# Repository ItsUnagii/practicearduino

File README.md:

# practicearduino

A custom Arduino PCB using a ATmega328P-A microcontroller made for personal practice.

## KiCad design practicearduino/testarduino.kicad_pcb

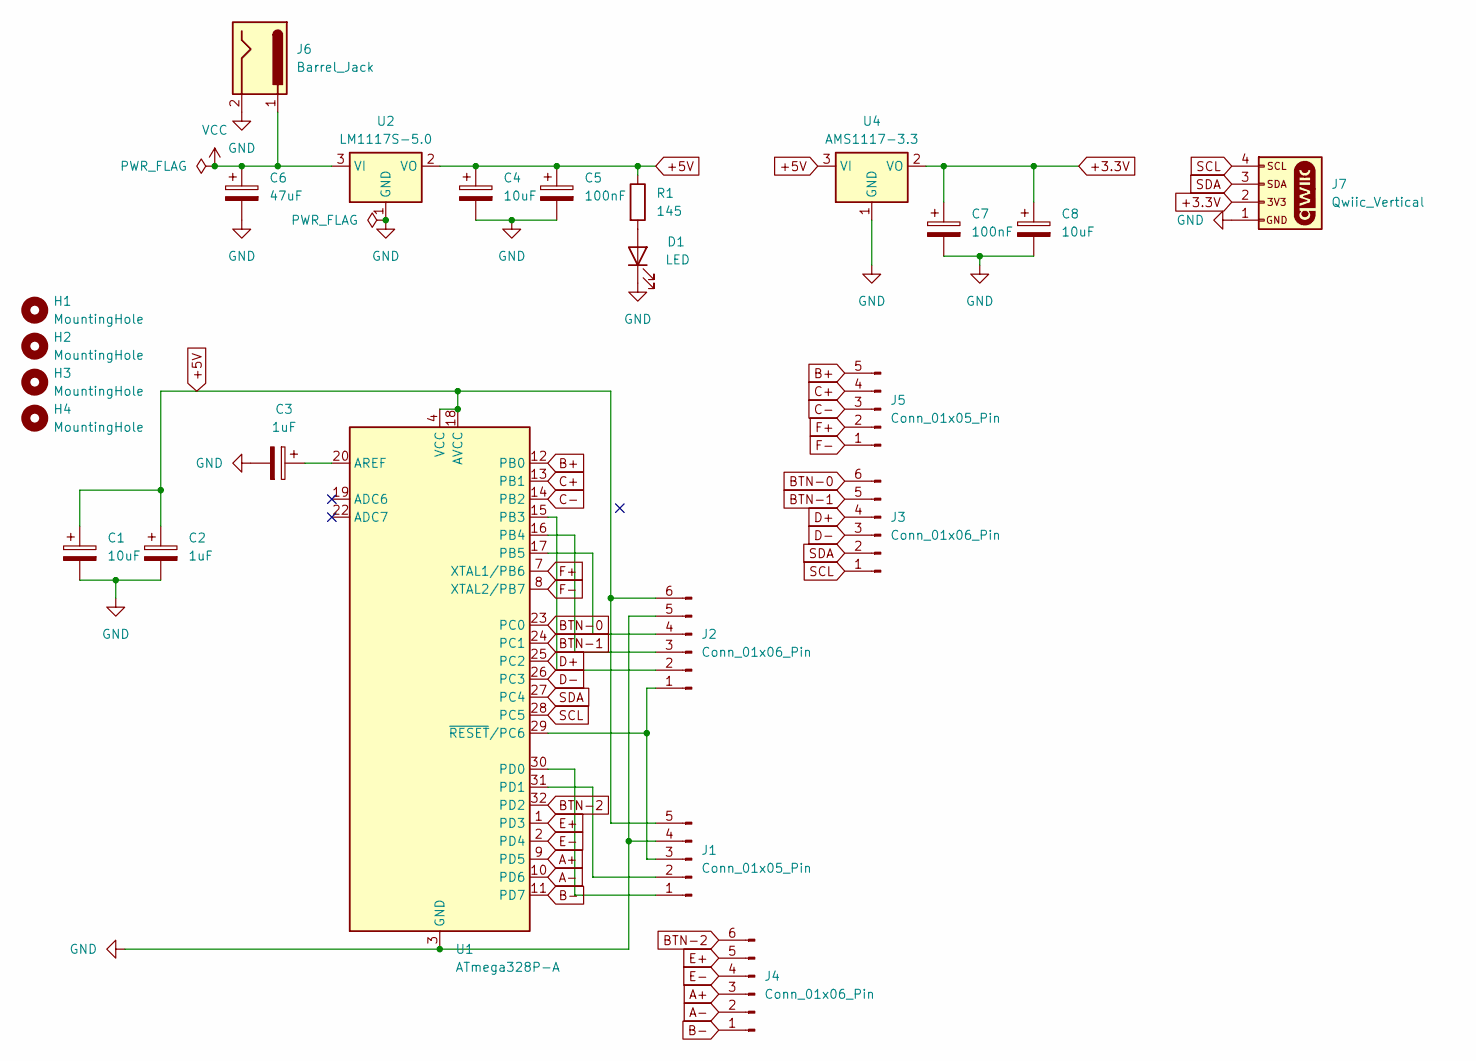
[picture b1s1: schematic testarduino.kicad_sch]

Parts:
C1, C4, C8: 10uF; C_0805_2012Metric
C2, C3: 1uF; C_0805_2012Metric
C5, C7: 100nF; C_0805_2012Metric
C6: 47uF; C_0805_2012Metric
D1: LED; LED_0805_2012Metric_Pad1.15x1.40mm_HandSolder
H1, H2, H3, H4: MountingHole; MountingHole_3.2mm_M3
J1, J5: Conn_01x05_Pin; PinHeader_1x05_P2.00mm_Horizontal
J2, J3, J4: Conn_01x06_Pin; PinHeader_1x06_P2.00mm_Horizontal
J6: Barrel_Jack; BarrelJack_Horizontal
J7: Qwiic_Vertical; JST_1x04_P1.0mm_Vertical_SMD
R1: 145; R_0805_2012Metric_Pad1.20x1.40mm_HandSolder
U1: ATmega328P-A; TQFP-32_7x7mm_P0.8mm
U2: LM1117S-5.0; TO-263-3_TabPin2
U4: AMS1117-3.3; SOT-223-3_TabPin2; LCSC C347222

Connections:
+3.3V: C7.1, C8.1, J7.2, U4.2 (VO)
+5V: C1.1, C2.1, C4.1, C5.1, J1.5, J2.6, R1.1, U1.4 (VCC), U1.6 (VCC), U1.18 (AVCC), U2.2 (VO), U4.3 (VI)
A+: J4.3, U1.9 (PD5)
A-: J4.2, U1.10 (PD6)
B+: J5.5, U1.12 (PB0)
B-: J4.1, U1.11 (PD7)
BTN-0: J3.6, U1.23 (PC0)
BTN-1: J3.5, U1.24 (PC1)
BTN-2: J4.6, U1.32 (PD2)
C+: J5.4, U1.13 (PB1)
C-: J5.3, U1.14 (PB2)
D+: J3.4, U1.25 (PC2)
D-: J3.3, U1.26 (PC3)
E+: J4.5, U1.1 (PD3)
E-: J4.4, U1.2 (PD4)
F+: J5.2, U1.7 (XTAL1/PB6)
F-: J5.1, U1.8 (XTAL2/PB7)
GND: C1.2, C2.2, C3.2, C4.2, C5.2, C6.2, C7.2, C8.2, D1.1 (K), J1.4, J2.5, J6.2, J7.1, U1.3 (GND), U1.5 (GND), U1.21 (GND), U2.1 (GND), U4.1 (GND)
unnamed: D1.2 (A), R1.2
unnamed: J1.1, U1.30 (PD0)
unnamed: J1.2, U1.31 (PD1)
unnamed: J1.3, J2.1, U1.29 (~RESET/PC6)
unnamed: J2.2, U1.15 (PB3)
unnamed: J2.3, U1.16 (PB4)
unnamed: J2.4, U1.17 (PB5)
unnamed: C3.1, U1.20 (AREF)
SCL: J3.1, J7.4, U1.28 (PC5)
SDA: J3.2, J7.3, U1.27 (PC4)
VCC: C6.1, J6.1, U2.3 (VI)

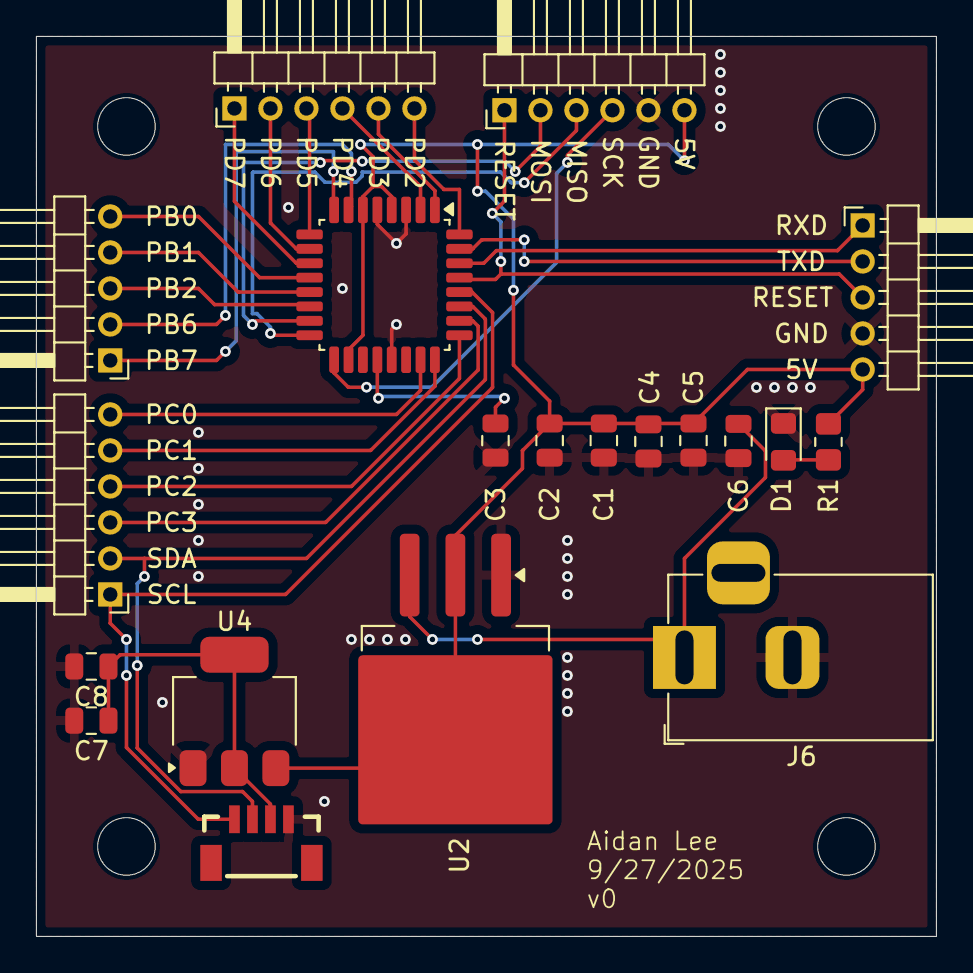
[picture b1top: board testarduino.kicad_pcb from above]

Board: 2 copper layers, 50.0 x 50.0 mm, 24 parts (0 on the bottom side), 29 nets.

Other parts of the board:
H1#2: MountingHole; MountingHole_3.2mm_M3

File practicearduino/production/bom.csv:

Designator,Footprint,Quantity,Value,LCSC Part #
"C1, C4, C8",0805,3,10uF,
"C2, C3",0805,2,1uF,
"C5, C7",0805,2,100nF,
C6,0805,1,47uF,
D1,0805,1,LED,
"J1, J5",PinHeader_1x05_P2.00mm_Horizontal,2,Conn_01x05_Pin,
"J2, J3, J4",PinHeader_1x06_P2.00mm_Horizontal,3,Conn_01x06_Pin,
J6,BarrelJack_Horizontal,1,Barrel_Jack,
J7,JST_1x04_P1.0mm_Vertical_SMD,1,Qwiic_Vertical,
R1,0805,1,145,
U1,TQFP-32_7x7mm_P0.8mm,1,ATmega328P-A,
U2,TO-263-3_TabPin2,1,LM1117S-5.0,
U4,SOT-223-3_TabPin2,1,AMS1117-3.3,C347222

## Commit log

2025-09-27 First files
2025-12-01 Added image of PCB
2025-12-01 Enhance README with project description and image
